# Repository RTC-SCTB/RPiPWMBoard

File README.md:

# RPiPWM_Board
## Описание
Проект платы расширения для одноплатного компьютера Raspberry Pi (версии B+, 2B, 3B, с 40 пинами).    
Включает в себя PCA9685 - I2C генератор ШИМ сигнала на 16 каналов, и либо одноканальным АЦП MCP3221, для измерения 
напряжения аккумулятора, либо измерителя питания INA219, который позволяет измерять также протекающий ток.  
Предусмотрен преобразователь напряжения LM2596-5.0 для питания Raspberry Pi от аккумулятора, 
номинальное напряжение питания до 25 В, при превышении возможен выход из строя некоторых (или всех) компонентов.  
Предусмотрено место для EEPROM CAT24C32 с обвязкой - для использования технологии 
[Raspberry Pi HAT](https://www.raspberrypi.org/blog/introducing-raspberry-pi-hats/), 
однако данная технология пока не используется.

## Содержание
- Необходимые нестандартные библиотеки - в папке `Libraries`  
- Список изменений - в файле `Changes.md`
- Gerber файлы - в папке `Gerbers`

## Функции

- Питание Raspberry Pi от аккумулятора (напряжение аккумулятора не должно превышать 25 В);
- Создание ШИМ сигнала на 16 каналах (0 - 15). Каналы 0 - 11 имеют возможность подключения внешнего источника питания
(предназначены для управления сервоприводами), каналы 12 - 15 предназначены для подключения драйверов, которые
 генерируют свое напряжение на данном разъеме;
- Определение напряжения питания (при подключении через клеммы), с помощью одноканального АЦП;
- Подключение I2C OLED дисплея SSD1306 размером 128x32 пикселя (может запаиваться на плату). Либо это посадочное место
может использоваться для подключения других I2C устройств при помощи разъема с шагом 2.54 мм;
- Кнопка и светодиод, подключенные к GPIO Raspberry Pi, функционал для которых может задаваться пользователем;

## Использование
Для данной платы написан [модуль](https://github.com/RTC-SCTB/RPiPWM) на языке Python 3,
реализующий весь перечисленный функционал.

## Полезные ссылки
- Даташит для ШИМ контроллера [PCA9685](https://cdn-shop.adafruit.com/datasheets/PCA9685.pdf)
- Даташит для дисплея [SSD1306](https://cdn-shop.adafruit.com/datasheets/SSD1306.pdf)
- Даташит для АЦП [MCP3221](http://ww1.microchip.com/downloads/en/DeviceDoc/20001732E.pdf)
- Даташит для измерителя питания [INA219](http://www.ti.com/lit/ds/symlink/ina219.pdf)

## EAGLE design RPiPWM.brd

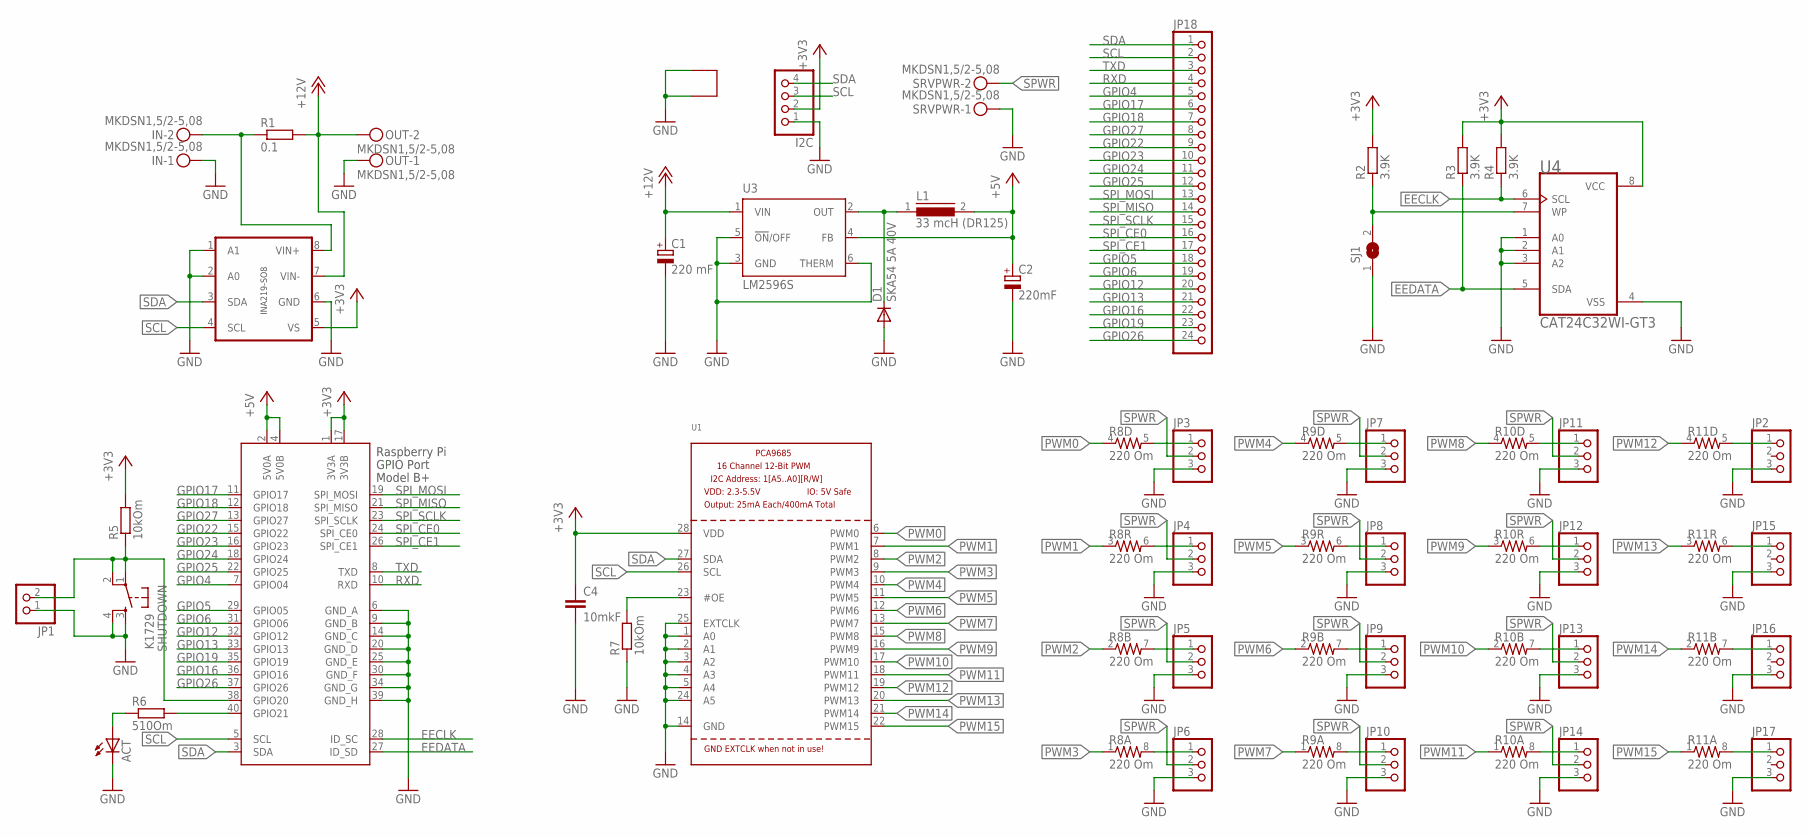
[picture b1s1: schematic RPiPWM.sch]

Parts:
ACT: LEDCHIPLED_1206; CHIPLED_1206
C1: 220 mF; 140CLH-1014
C2: 220mF; 140CLH-1014
C4: 10mkF; C0805K
D1: SKA54 5A 40V; SMB
GNDLOOP: LOOP
I2C: PINHD-1X04_2.54-S; 1X04-S
IN: MKDSN1,5/2-5,08
JP1: PINHD-1X02_2.54-S; 1X02-S
JP2, JP3, JP4, JP5, JP6, JP7, JP8, JP9, JP10, JP11, JP12, JP13, JP14, JP15, JP16, JP17: PINHD-1X03_2.54-S; 1X03-S
JP18: PINHD-1X24_2.54-S; 1X24-S
L1: 33 mcH (DR125); DR125
OUT: MKDSN1,5/2-5,08
R1: 0.1; R2512
R2, R3, R4: 3.9K; R0805
R5, R7: 10kOm; R0805
R6: 510Om; R0805
R8, R9, R10, R11: 220 Om; 0603-ARV
SHUTDOWN: K1729; DTSM-6
SJ1: SJ
SRVPWR: MKDSN1,5/2-5,08
U1: PCA9685; TSSOP28
U2: INA219-SO8D; SO08
U3: LM2596S; TO263-5
U4: CAT24C32WI-GT3; SOIC127P600X175-8N
X1: RASPI_BOARD_B+#_HDC; RASPI_BOARD_B+HAT_DF_CF

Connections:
+3V3: C4.1, I2C.2, R2.2, R3.2, R4.2, R5.2, U1.28 (VDD), U2.5 (VS), U4.8 (VCC), X1.1 (3V3A), X1.17 (3V3B)
+5V: C2.+, L1.2, U3.4 (FB), X1.2 (5V0A), X1.4 (5V0B)
+12V: C1.+, OUT.2, R1.2, U2.7 (VIN-), U3.1 (VIN)
EECLK: R4.1, U4.6 (SCL), X1.28 (ID_SC)
EEDATA: R3.1, U4.5 (SDA), X1.27 (ID_SD)
GND: ACT.C, C1.-, C2.-, C4.2, D1.A, GNDLOOP.P$1 (1), GNDLOOP.P$2 (2), I2C.1, IN.1, JP1.1, JP2.3, JP3.3, JP4.3, JP5.3, JP6.3, JP7.3, JP8.3, JP9.3, JP10.3, JP11.3, JP12.3, JP13.3, JP14.3, JP15.3, JP16.3, JP17.3, OUT.1, R7.1, SHUTDOWN.3, SHUTDOWN.4, SJ1.1, SRVPWR.1, U1.1 (A0), U1.2 (A1), U1.3 (A2), U1.4 (A3), U1.5 (A4), U1.14 (GND), U1.24 (A5), U1.25 (EXTCLK), U2.1 (A1), U2.2 (A0), U2.6 (GND), U3.3 (GND), U3.5 (!ON!/OFF), U3.6 (THERM), U4.1 (A0), U4.2 (A1), U4.3 (A2), U4.4 (VSS), X1.6 (GND_A), X1.9 (GND_B), X1.14 (GND_C), X1.20 (GND_D), X1.25 (GND_E), X1.30 (GND_F), X1.34 (GND_G), X1.39 (GND_H)
GPIO4: JP18.5, X1.7 (GPIO04)
GPIO5: JP18.18, X1.29 (GPIO05)
GPIO6: JP18.19, X1.31 (GPIO06)
GPIO12: JP18.20, X1.32 (GPIO12)
GPIO13: JP18.21, X1.33 (GPIO13)
GPIO16: JP18.22, X1.36 (GPIO16)
GPIO17: JP18.6, X1.11 (GPIO17)
GPIO18: JP18.7, X1.12 (GPIO18)
GPIO19: JP18.23, X1.35 (GPIO19)
GPIO22: JP18.9, X1.15 (GPIO22)
GPIO23: JP18.10, X1.16 (GPIO23)
GPIO24: JP18.11, X1.18 (GPIO24)
GPIO25: JP18.12, X1.22 (GPIO25)
GPIO26: JP18.24, X1.37 (GPIO26)
GPIO27: JP18.8, X1.13 (GPIO27)
unnamed: R6.2, X1.40 (GPIO21)
unnamed: ACT.A, R6.1
unnamed: D1.C, L1.1, U3.2 (OUT)
unnamed: JP1.2, R5.1, SHUTDOWN.1, SHUTDOWN.2, X1.38 (GPIO20)
unnamed: JP3.1, R8.5 (2)
unnamed: JP4.1, R8.6 (2)
unnamed: JP7.1, R9.5 (2)
unnamed: JP5.1, R8.7 (2)
unnamed: R2.1, SJ1.2, U4.7 (WP)
unnamed: JP6.1, R8.8 (2)
unnamed: JP11.1, R10.5 (2)
unnamed: JP2.1, R11.5 (2)
unnamed: JP15.1, R11.6 (2)
unnamed: JP16.1, R11.7 (2)
unnamed: JP17.1, R11.8 (2)
unnamed: JP14.1, R10.8 (2)
unnamed: JP13.1, R10.7 (2)
unnamed: JP12.1, R10.6 (2)
unnamed: JP8.1, R9.6 (2)
unnamed: JP9.1, R9.7 (2)
unnamed: JP10.1, R9.8 (2)
unnamed: IN.2, R1.1, U2.8 (VIN+)
unnamed: R7.2, U1.23 (#OE)
PWM0: R8.4 (1), U1.6 (PWM0)
PWM1: R8.3 (1), U1.7 (PWM1)
PWM2: R8.2 (1), U1.8 (PWM2)
PWM3: R8.1, U1.9 (PWM3)
PWM4: R9.4 (1), U1.10 (PWM4)
PWM5: R9.3 (1), U1.11 (PWM5)
PWM6: R9.2 (1), U1.12 (PWM6)
PWM7: R9.1, U1.13 (PWM7)
PWM8: R10.4 (1), U1.15 (PWM8)
PWM9: R10.3 (1), U1.16 (PWM9)
PWM10: R10.2 (1), U1.17 (PWM10)
PWM11: R10.1, U1.18 (PWM11)
PWM12: R11.4 (1), U1.19 (PWM12)
PWM13: R11.3 (1), U1.20 (PWM13)
PWM14: R11.2 (1), U1.21 (PWM14)
PWM15: R11.1, U1.22 (PWM15)
RXD: JP18.4, X1.10 (RXD)
SCL: I2C.3, JP18.2, U1.26 (SCL), U2.4 (SCL), X1.5 (SCL)
SDA: I2C.4, JP18.1, U1.27 (SDA), U2.3 (SDA), X1.3 (SDA)
SPI_CE0: JP18.16, X1.24 (SPI_CE0)
SPI_CE1: JP18.17, X1.26 (SPI_CE1)
SPI_MISO: JP18.14, X1.21 (SPI_MISO)
SPI_MOSI: JP18.13, X1.19 (SPI_MOSI)
SPI_SCLK: JP18.15, X1.23 (SPI_SCLK)
SPWR: JP3.2, JP4.2, JP5.2, JP6.2, JP7.2, JP8.2, JP9.2, JP10.2, JP11.2, JP12.2, JP13.2, JP14.2, SRVPWR.2
TXD: JP18.3, X1.8 (TXD)

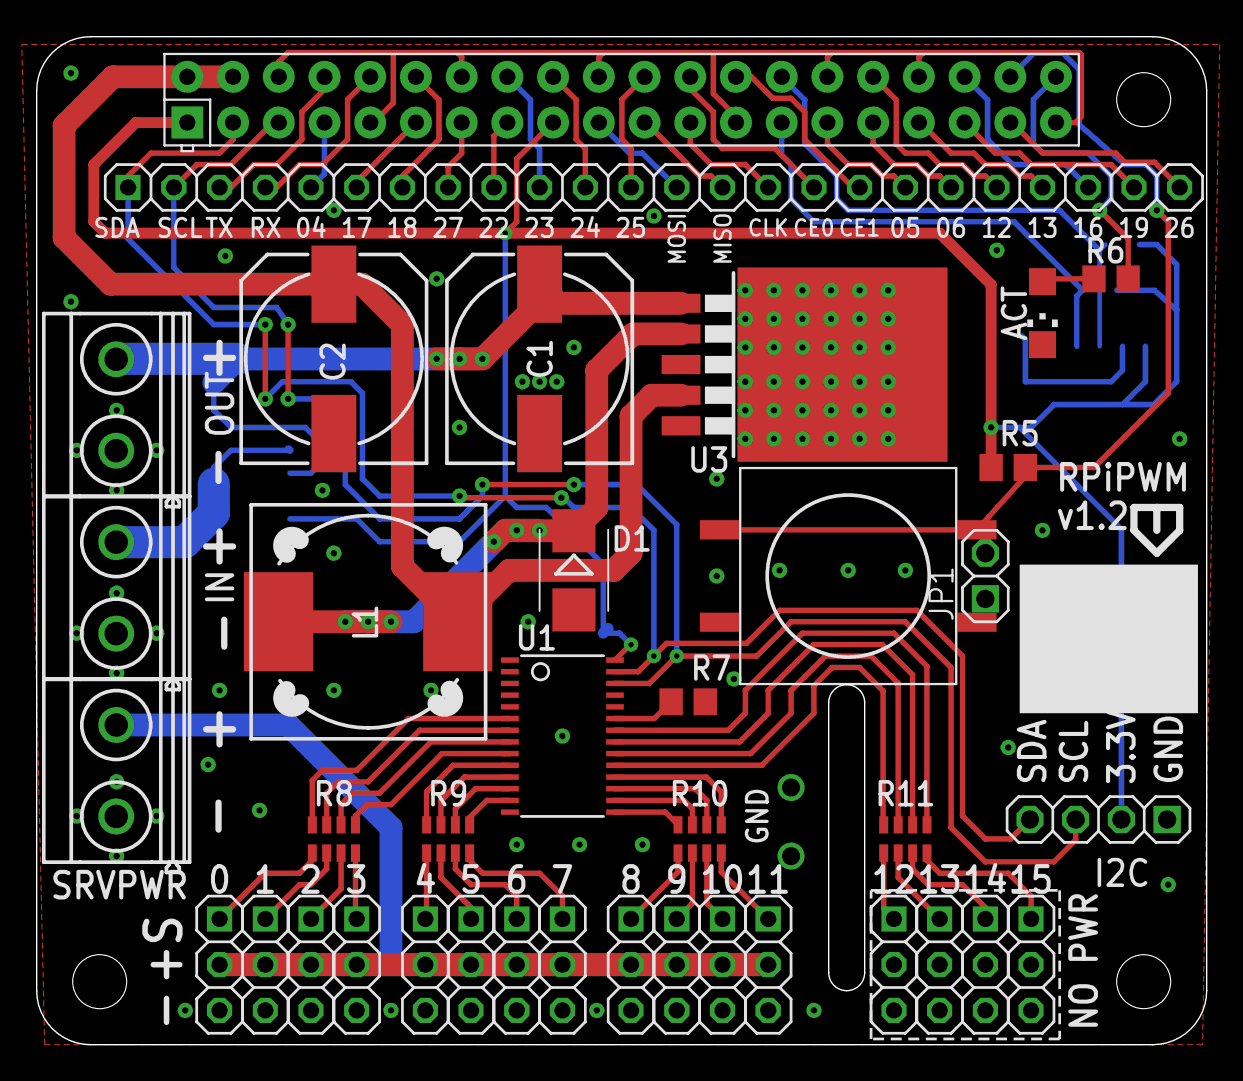
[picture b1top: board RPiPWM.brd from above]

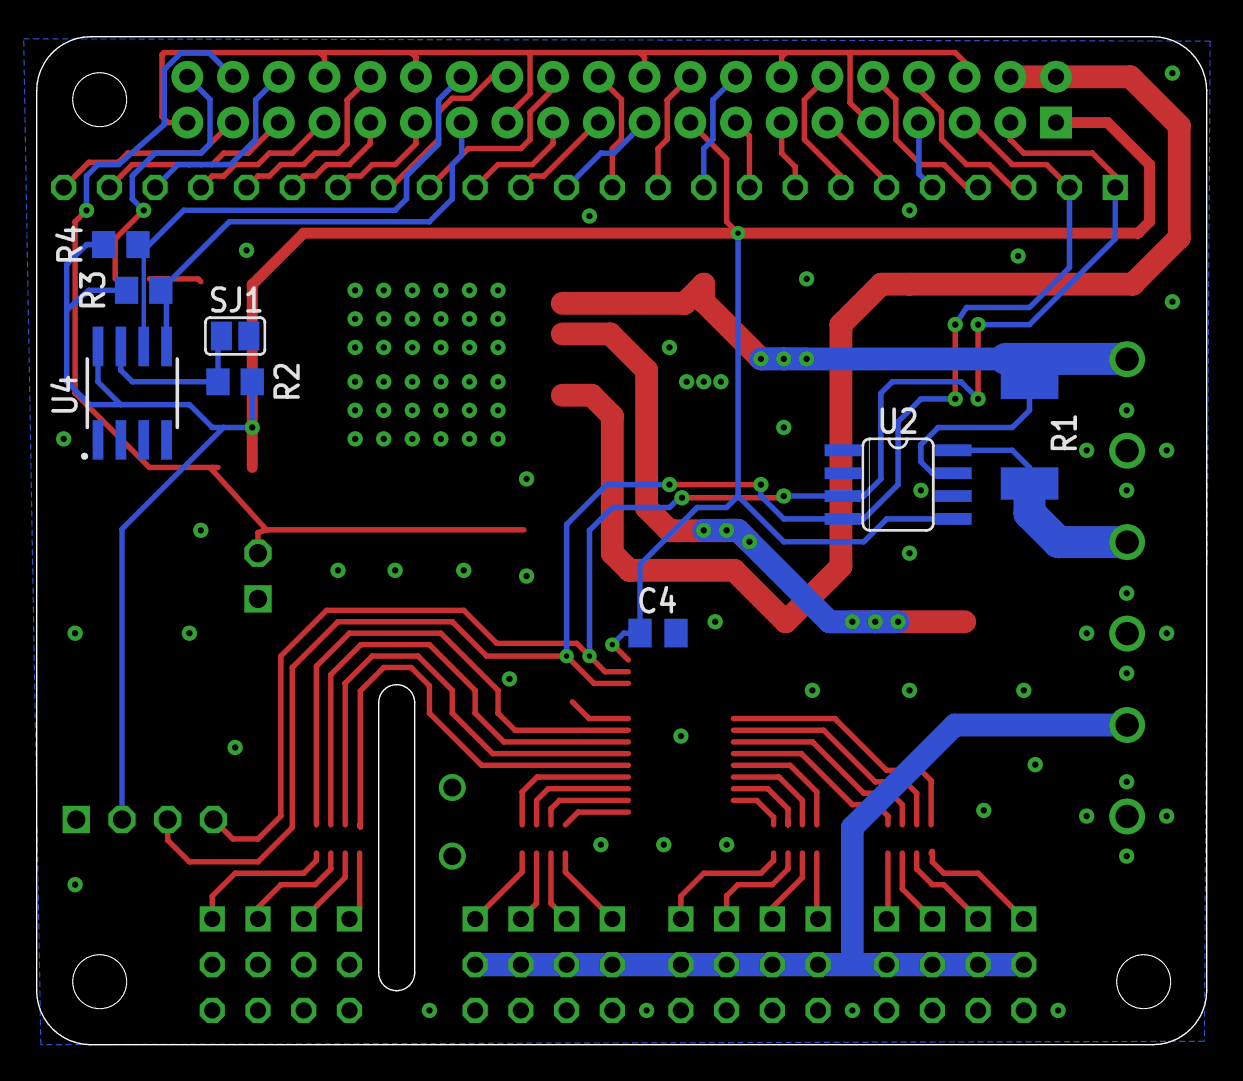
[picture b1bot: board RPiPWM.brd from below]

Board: 2 copper layers, 65.0 x 56.0 mm, 48 parts (8 on the bottom side), 70 nets.

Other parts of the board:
U$1: MASKLABEL

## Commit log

2018-10-24 Обновлены README и Changes
2018-10-24 Добавлены Gerber файлы
2018-10-24 Исправлен файл для сверловки платы

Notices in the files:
parts and their libraries:
SparkFun-Resistors: Licensing: Creative Commons ShareAlike 4.0 International - https://creativecommons.org/licenses/by-sa/4.0
